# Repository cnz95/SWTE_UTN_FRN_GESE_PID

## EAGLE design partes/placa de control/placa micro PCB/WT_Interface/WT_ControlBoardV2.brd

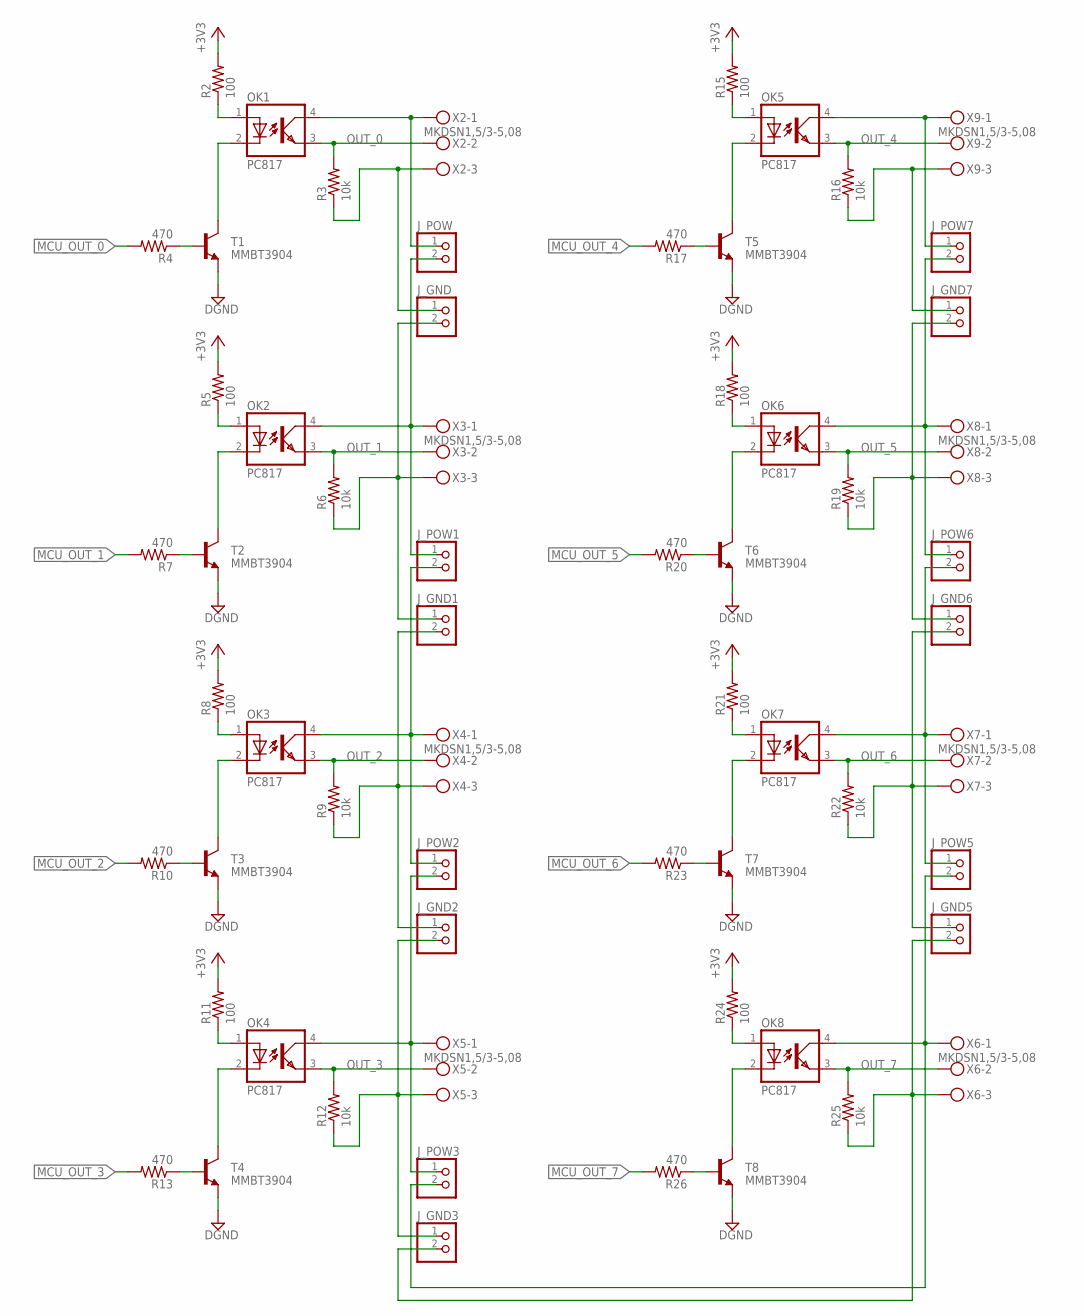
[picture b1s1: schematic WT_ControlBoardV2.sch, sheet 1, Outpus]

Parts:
J_GND, J_GND1, J_GND2, J_GND3, J_GND5, J_GND6, J_GND7: PINHD-1X2; 1X02
J_POW, J_POW1, J_POW2, J_POW3, J_POW5, J_POW6, J_POW7: PINHD-1X2; 1X02
OK1, OK2, OK3, OK4, OK5, OK6, OK7, OK8: PC817; DIL04
R2, R5, R8, R11, R15, R18, R21, R24: 100; R0402
R3, R6, R9, R12, R16, R19, R22, R25: 10k; R0402
R4, R7, R10, R13, R20, R23, R26: 470; 0204/5
R17: 470; 0204/7
T1, T2, T3, T4, T5, T6, T7, T8: MMBT3904; SOT23-BEC
X2, X3, X4, X5, X6, X7, X8, X9: MKDSN1,5/3-5,08

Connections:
+3V3: R2.2, R5.2, R8.2, R11.2, R15.2, R18.2, R21.2, R24.2; also elsewhere on the board
DGND: T1.E, T2.E, T3.E, T4.E, T5.E, T6.E, T7.E, T8.E; also elsewhere on the board
MCU_OUT_0: R4.2; also elsewhere on the board
MCU_OUT_1: R7.2; also elsewhere on the board
MCU_OUT_2: R10.2; also elsewhere on the board
MCU_OUT_3: R13.2; also elsewhere on the board
MCU_OUT_4: R17.2; also elsewhere on the board
MCU_OUT_5: R20.2; also elsewhere on the board
MCU_OUT_6: R23.2; also elsewhere on the board
MCU_OUT_7: R26.2; also elsewhere on the board
unnamed: OK1.2 (C), T1.C
unnamed: OK2.2 (C), T2.C
unnamed: R4.1, T1.B
unnamed: OK1.1 (A), R2.1
unnamed: R7.1, T2.B
unnamed: OK2.1 (A), R5.1
unnamed: OK3.2 (C), T3.C
unnamed: R10.1, T3.B
unnamed: OK3.1 (A), R8.1
unnamed: OK4.2 (C), T4.C
unnamed: R13.1, T4.B
unnamed: OK4.1 (A), R11.1
unnamed: OK5.2 (C), T5.C
unnamed: R17.1, T5.B
unnamed: OK5.1 (A), R15.1
unnamed: OK6.2 (C), T6.C
unnamed: R20.1, T6.B
unnamed: OK6.1 (A), R18.1
unnamed: OK7.2 (C), T7.C
unnamed: R23.1, T7.B
unnamed: OK7.1 (A), R21.1
unnamed: OK8.2 (C), T8.C
unnamed: R26.1, T8.B
unnamed: OK8.1 (A), R24.1
unnamed: J_GND6.1, J_GND7.2, R19.1, X8.3
unnamed: J_GND.1, R3.1, X2.3
unnamed: J_GND.2, J_GND1.1, R6.1, X3.3
unnamed: J_POW.2, J_POW1.1, OK2.4 (COL), X3.1
unnamed: J_POW1.2, J_POW2.1, OK3.4 (COL), X4.1
unnamed: J_GND1.2, J_GND2.1, R9.1, X4.3
unnamed: J_POW2.2, J_POW3.1, OK4.4 (COL), X5.1
unnamed: J_GND2.2, J_GND3.1, R12.1, X5.3
unnamed: J_GND3.2, J_GND5.2, R25.1, X6.3
unnamed: J_POW3.2, J_POW5.2, OK8.4 (COL), X6.1
unnamed: J_POW5.1, J_POW6.2, OK7.4 (COL), X7.1
unnamed: J_GND5.1, J_GND6.2, R22.1, X7.3
unnamed: J_POW6.1, J_POW7.2, OK6.4 (COL), X8.1
unnamed: J_POW7.1, OK5.4 (COL), X9.1
unnamed: J_GND7.1, R16.1, X9.3
unnamed: J_POW.1, OK1.4 (COL), X2.1
OUT_0: OK1.3 (EMIT), R3.2, X2.2
OUT_1: OK2.3 (EMIT), R6.2, X3.2
OUT_2: OK3.3 (EMIT), R9.2, X4.2
OUT_3: OK4.3 (EMIT), R12.2, X5.2
OUT_4: OK5.3 (EMIT), R16.2, X9.2
OUT_5: OK6.3 (EMIT), R19.2, X8.2
OUT_6: OK7.3 (EMIT), R22.2, X7.2
OUT_7: OK8.3 (EMIT), R25.2, X6.2

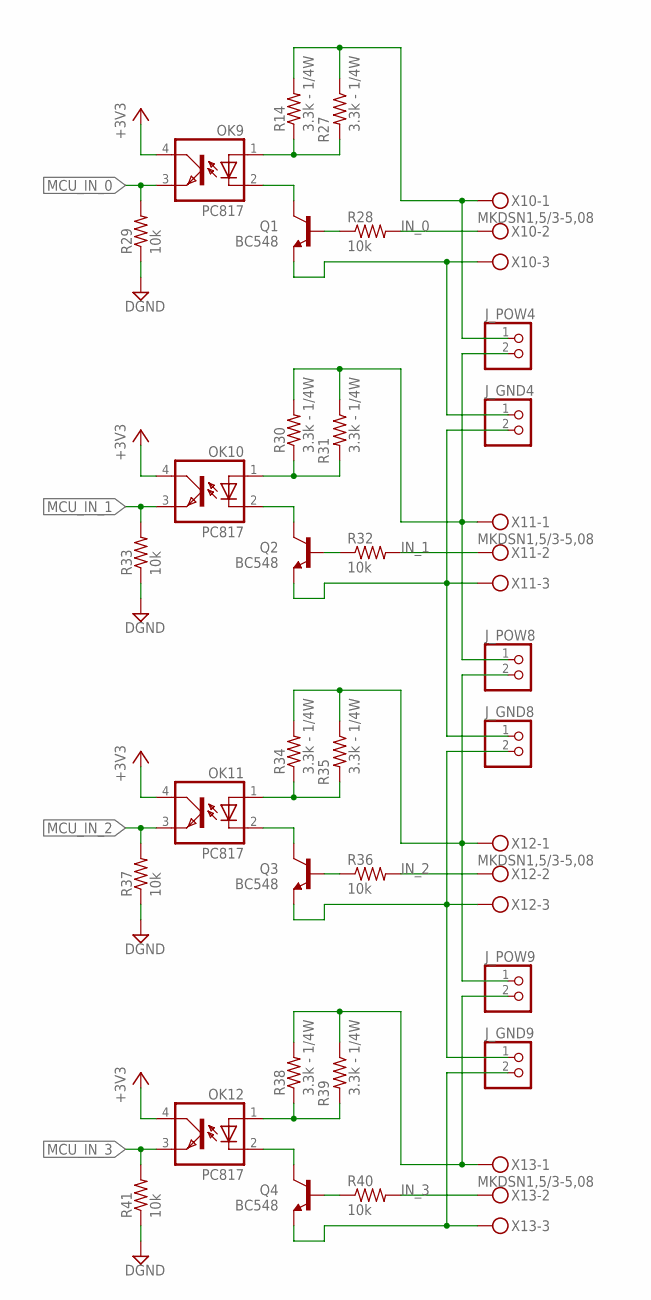
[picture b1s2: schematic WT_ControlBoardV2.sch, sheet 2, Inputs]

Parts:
J_GND4, J_GND8, J_GND9: PINHD-1X2; 1X02
J_POW4, J_POW8, J_POW9: PINHD-1X2; 1X02
OK9, OK10, OK11, OK12: PC817; DIL04
Q1, Q2, Q3, Q4: BC548; TO92-EBC
R14, R27, R30, R31, R34, R35, R38, R39: 3.3k - 1/4W; 0204V
R28, R32, R36, R40: 10k; 0204/5
R29, R33, R37, R41: 10k; R0402
X10, X11, X12, X13: MKDSN1,5/3-5,08

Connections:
+3V3: OK9.4 (COL), OK10.4 (COL), OK11.4 (COL), OK12.4 (COL); also elsewhere on the board
DGND: R29.1, R33.1, R37.1, R41.1; also elsewhere on the board
IN_0: R28.2, X10.2
IN_1: R32.2, X11.2
IN_2: R36.2, X12.2
IN_3: R40.2, X13.2
MCU_IN_0: OK9.3 (EMIT), R29.2; also elsewhere on the board
MCU_IN_1: OK10.3 (EMIT), R33.2; also elsewhere on the board
MCU_IN_2: OK11.3 (EMIT), R37.2; also elsewhere on the board
MCU_IN_3: OK12.3 (EMIT), R41.2; also elsewhere on the board
unnamed: OK9.1 (A), R14.1, R27.2
unnamed: OK9.2 (C), Q1.C
unnamed: Q1.B, R28.1
unnamed: OK10.1 (A), R30.1, R31.2
unnamed: OK10.2 (C), Q2.C
unnamed: Q2.B, R32.1
unnamed: OK11.1 (A), R34.1, R35.2
unnamed: OK11.2 (C), Q3.C
unnamed: Q3.B, R36.1
unnamed: OK12.1 (A), R38.1, R39.2
unnamed: OK12.2 (C), Q4.C
unnamed: Q4.B, R40.1
unnamed: J_GND4.2, J_GND8.1, Q2.E, X11.3
unnamed: J_GND9.2, Q4.E, X13.3
unnamed: J_POW9.2, R38.2, R39.1, X13.1
unnamed: J_POW4.2, J_POW8.1, R30.2, R31.1, X11.1
unnamed: J_GND8.2, J_GND9.1, Q3.E, X12.3
unnamed: J_POW8.2, J_POW9.1, R34.2, R35.1, X12.1
unnamed: J_GND4.1, Q1.E, X10.3
unnamed: J_POW4.1, R14.2, R27.1, X10.1

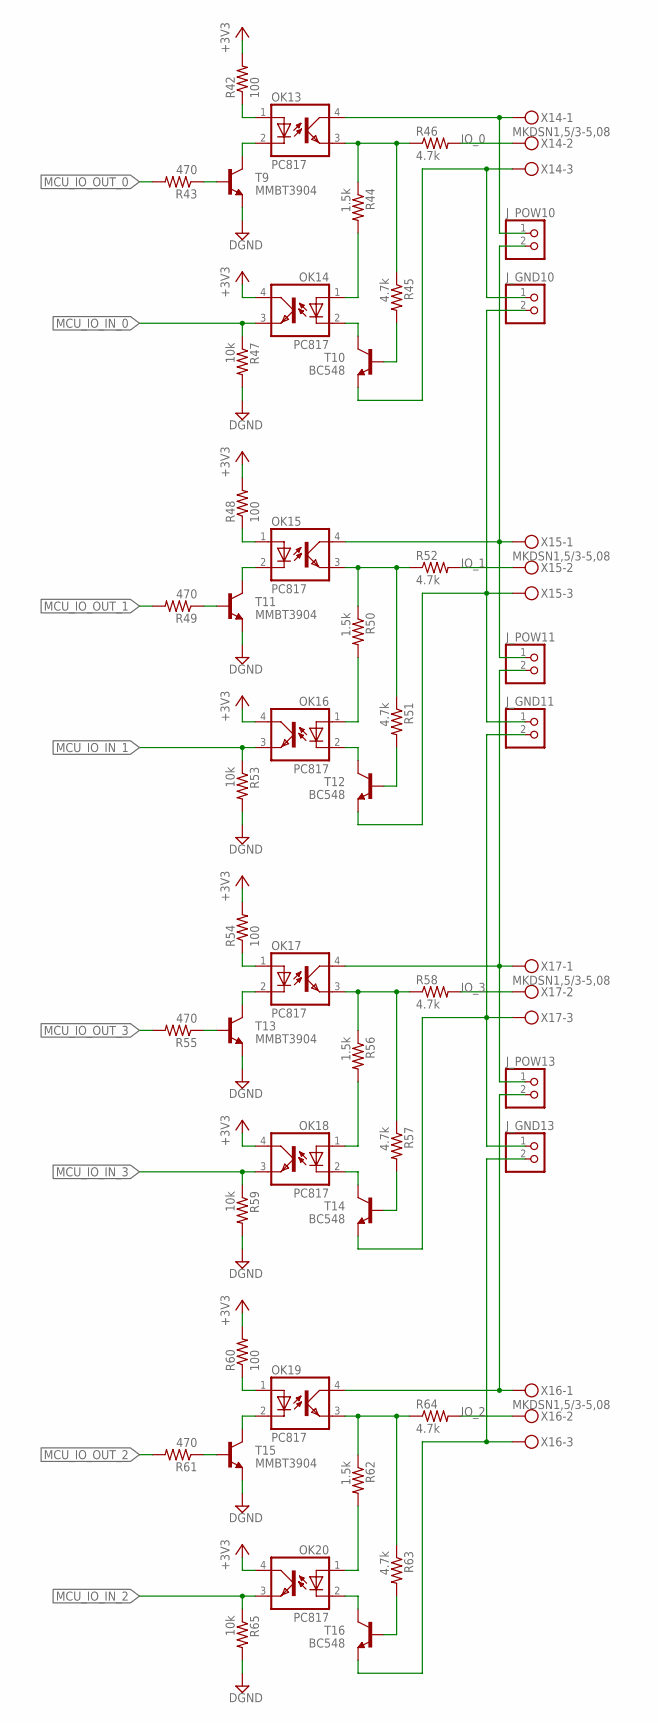
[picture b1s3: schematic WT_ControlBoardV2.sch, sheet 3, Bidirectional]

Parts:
J_GND10, J_GND11, J_GND13: PINHD-1X2; 1X02
J_POW10, J_POW11, J_POW13: PINHD-1X2; 1X02
OK13, OK14, OK15, OK16, OK17, OK18, OK19, OK20: PC817; DIL04
R42, R48, R54, R60: 100; 0204/7
R43, R49, R55, R61: 470; R0402
R44, R50, R56, R62: 1.5k; 0204/5
R45, R46, R51, R52, R57, R58, R63, R64: 4.7k; 0204V
R47, R53, R59, R65: 10k; 0204/5
T9, T11, T13, T15: MMBT3904; SOT23-BEC
T10, T12, T14, T16: BC548; TO92-CBE
X14, X15, X16, X17: MKDSN1,5/3-5,08

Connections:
+3V3: OK14.4 (COL), OK16.4 (COL), OK18.4 (COL), OK20.4 (COL), R42.2, R48.2, R54.2, R60.2; also elsewhere on the board
DGND: R47.2, R53.2, R59.2, R65.2, T9.E, T11.E, T13.E, T15.E; also elsewhere on the board
IO_0: R46.2, X14.2
IO_1: R52.2, X15.2
IO_2: R64.2, X16.2
IO_3: R58.2, X17.2
MCU_IO_IN_0: OK14.3 (EMIT), R47.1; also elsewhere on the board
MCU_IO_IN_1: OK16.3 (EMIT), R53.1; also elsewhere on the board
MCU_IO_IN_2: OK20.3 (EMIT), R65.1; also elsewhere on the board
MCU_IO_IN_3: OK18.3 (EMIT), R59.1; also elsewhere on the board
MCU_IO_OUT_0: R43.2; also elsewhere on the board
MCU_IO_OUT_1: R49.2; also elsewhere on the board
MCU_IO_OUT_2: R61.2; also elsewhere on the board
MCU_IO_OUT_3: R55.2; also elsewhere on the board
unnamed: OK14.2 (C), T10.C
unnamed: OK13.2 (C), T9.C
unnamed: R43.1, T9.B
unnamed: OK13.1 (A), R42.1
unnamed: OK13.3 (EMIT), R44.1, R45.1, R46.1
unnamed: OK14.1 (A), R44.2
unnamed: R45.2, T10.B
unnamed: OK16.2 (C), T12.C
unnamed: OK15.2 (C), T11.C
unnamed: R49.1, T11.B
unnamed: OK15.1 (A), R48.1
unnamed: OK15.3 (EMIT), R50.1, R51.1, R52.1
unnamed: OK16.1 (A), R50.2
unnamed: R51.2, T12.B
unnamed: OK18.2 (C), T14.C
unnamed: OK17.2 (C), T13.C
unnamed: R55.1, T13.B
unnamed: OK17.1 (A), R54.1
unnamed: OK17.3 (EMIT), R56.1, R57.1, R58.1
unnamed: OK18.1 (A), R56.2
unnamed: R57.2, T14.B
unnamed: OK20.2 (C), T16.C
unnamed: OK19.2 (C), T15.C
unnamed: R61.1, T15.B
unnamed: OK19.1 (A), R60.1
unnamed: OK19.3 (EMIT), R62.1, R63.1, R64.1
unnamed: OK20.1 (A), R62.2
unnamed: R63.2, T16.B
unnamed: J_POW11.2, J_POW13.1, OK17.4 (COL), X17.1
unnamed: J_GND13.2, T16.E, X16.3
unnamed: J_POW10.1, OK13.4 (COL), X14.1
unnamed: J_GND10.1, T10.E, X14.3
unnamed: J_POW10.2, J_POW11.1, OK15.4 (COL), X15.1
unnamed: J_GND10.2, J_GND11.1, T12.E, X15.3
unnamed: J_GND11.2, J_GND13.1, T14.E, X17.3
unnamed: J_POW13.2, OK19.4 (COL), X16.1

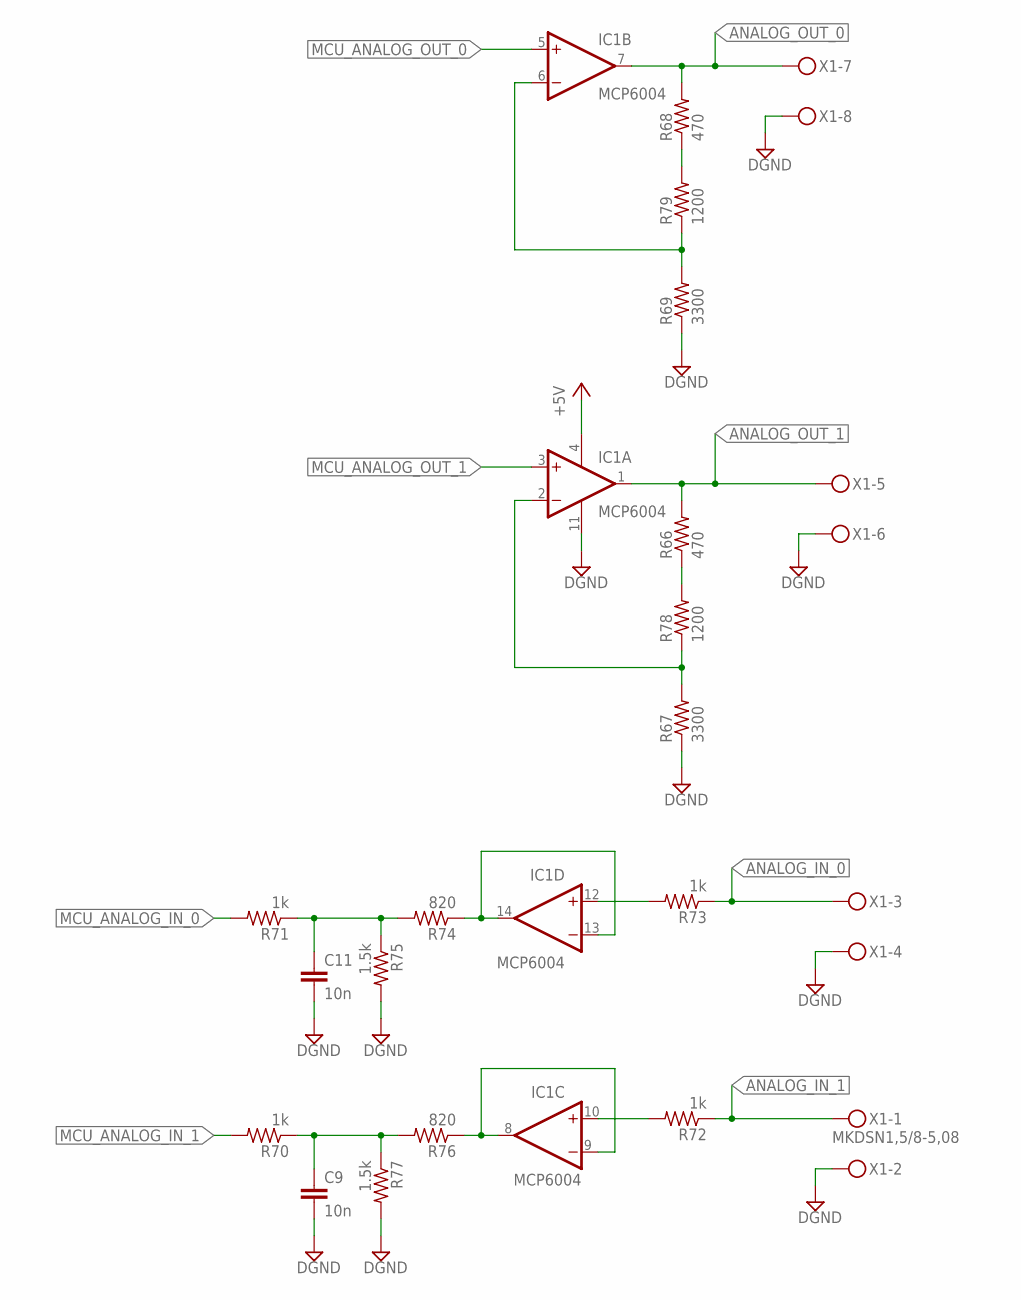
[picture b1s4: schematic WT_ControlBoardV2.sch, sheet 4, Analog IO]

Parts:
C9, C11: 10n; C0402
IC1: MCP6004; SO14
R66, R68: 470; R0402
R67, R69: 3300; R0402
R70, R71: 1k; R0402
R72: 1k; 0204V
R73: 1k; 0204/7
R74, R76: 820; R0402
R75, R77: 1.5k; R0402
R78, R79: 1200; R0402
X1: MKDSN1,5/8-5,08

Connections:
+5V: IC1.4 (V+); also elsewhere on the board
ANALOG_IN_0: R73.1, X1.3
ANALOG_IN_1: R72.1, X1.1
ANALOG_OUT_0: IC1.7 (OUT), R68.2, X1.7
ANALOG_OUT_1: IC1.1 (OUT), R66.2, X1.5
DGND: C9.2, C11.2, IC1.11 (V-), R67.1, R69.1, R75.2, R77.2, X1.2, X1.4, X1.6, X1.8; also elsewhere on the board
MCU_ANALOG_IN_0: R71.2; also elsewhere on the board
MCU_ANALOG_IN_1: R70.2; also elsewhere on the board
MCU_ANALOG_OUT_0: IC1.5 (+IN); also elsewhere on the board
MCU_ANALOG_OUT_1: IC1.3 (+IN); also elsewhere on the board
unnamed: IC1.6 (-IN), R69.2, R79.1
unnamed: IC1.2 (-IN), R67.2, R78.1
unnamed: IC1.10 (+IN), R72.2
unnamed: IC1.12 (+IN), R73.2
unnamed: IC1.8 (OUT), IC1.9 (-IN), R76.1
unnamed: IC1.13 (-IN), IC1.14 (OUT), R74.1
unnamed: C9.1, R70.1, R76.2, R77.1
unnamed: C11.1, R71.1, R74.2, R75.1
unnamed: R66.1, R78.2
unnamed: R68.1, R79.2

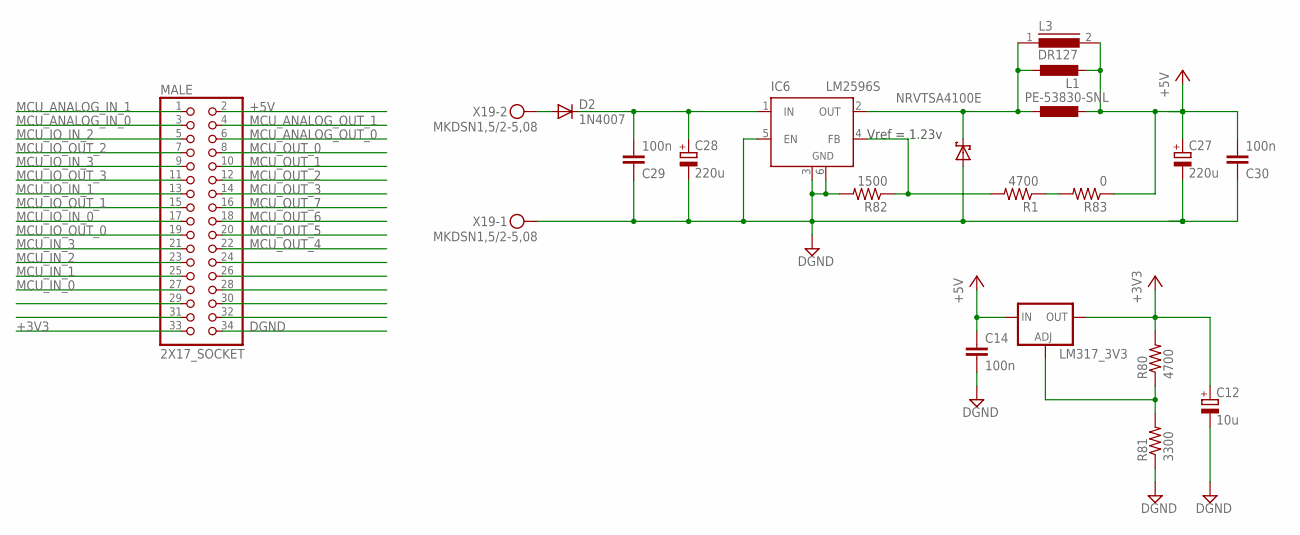
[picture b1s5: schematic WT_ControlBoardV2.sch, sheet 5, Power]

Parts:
C12: 10u; E1,8-4
C14, C29, C30: 100n; C1206
C27, C28: 220u; E5-10,5
D2: 1N4007; C1702-05
D8: NRVTSA4100E; SMA-2
IC6: LM2596S; TO263-5
L1: L-EUPIS2816; PIS2816
L2: PE-53830-SNL; LCI-44
L3: DR127
LM317_3V3: LM317TS; 317TS
MALE: 2X17_SOCKET
R1: 4700; R0402
R80: 4700; 0204V
R81: 3300; 0204V
R82: 1500; R0402
R83: 0; R0402
X19: MKDSN1,5/2-5,08

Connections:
+3V3: C12.+, LM317_3V3.2 (OUT), MALE.33, R80.2; also elsewhere on the board
+5V: C14.1, C27.+, C30.2, L1.2, L2.1, L3.2, LM317_3V3.3 (IN), MALE.2, R83.1; also elsewhere on the board
DGND: C12.-, C14.2, C27.-, C28.-, C29.1, C30.1, D8.A, IC6.3 (GND), IC6.5 (EN), IC6.6 (GND), MALE.34, R81.1, R82.2, X19.1; also elsewhere on the board
MCU_ANALOG_IN_0: MALE.3; also elsewhere on the board
MCU_ANALOG_IN_1: MALE.1; also elsewhere on the board
MCU_ANALOG_OUT_0: MALE.6; also elsewhere on the board
MCU_ANALOG_OUT_1: MALE.4; also elsewhere on the board
MCU_IN_0: MALE.27; also elsewhere on the board
MCU_IN_1: MALE.25; also elsewhere on the board
MCU_IN_2: MALE.23; also elsewhere on the board
MCU_IN_3: MALE.21; also elsewhere on the board
MCU_IO_IN_0: MALE.17; also elsewhere on the board
MCU_IO_IN_1: MALE.13; also elsewhere on the board
MCU_IO_IN_2: MALE.5; also elsewhere on the board
MCU_IO_IN_3: MALE.9; also elsewhere on the board
MCU_IO_OUT_0: MALE.19; also elsewhere on the board
MCU_IO_OUT_1: MALE.15; also elsewhere on the board
MCU_IO_OUT_2: MALE.7; also elsewhere on the board
MCU_IO_OUT_3: MALE.11; also elsewhere on the board
MCU_OUT_0: MALE.8; also elsewhere on the board
MCU_OUT_1: MALE.10; also elsewhere on the board
MCU_OUT_2: MALE.12; also elsewhere on the board
MCU_OUT_3: MALE.14; also elsewhere on the board
MCU_OUT_4: MALE.22; also elsewhere on the board
MCU_OUT_5: MALE.20; also elsewhere on the board
MCU_OUT_6: MALE.18; also elsewhere on the board
MCU_OUT_7: MALE.16; also elsewhere on the board
unnamed: D2.A, X19.2
unnamed: D8.C, IC6.2 (OUT), L1.1, L2.2, L3.1
unnamed: C28.+, C29.2, D2.C, IC6.1 (IN)
unnamed: LM317_3V3.1 (ADJ), R80.1, R81.2
unnamed: IC6.4 (FB), R1.2, R82.1
unnamed: R1.1, R83.2

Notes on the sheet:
Vref = 1.23v

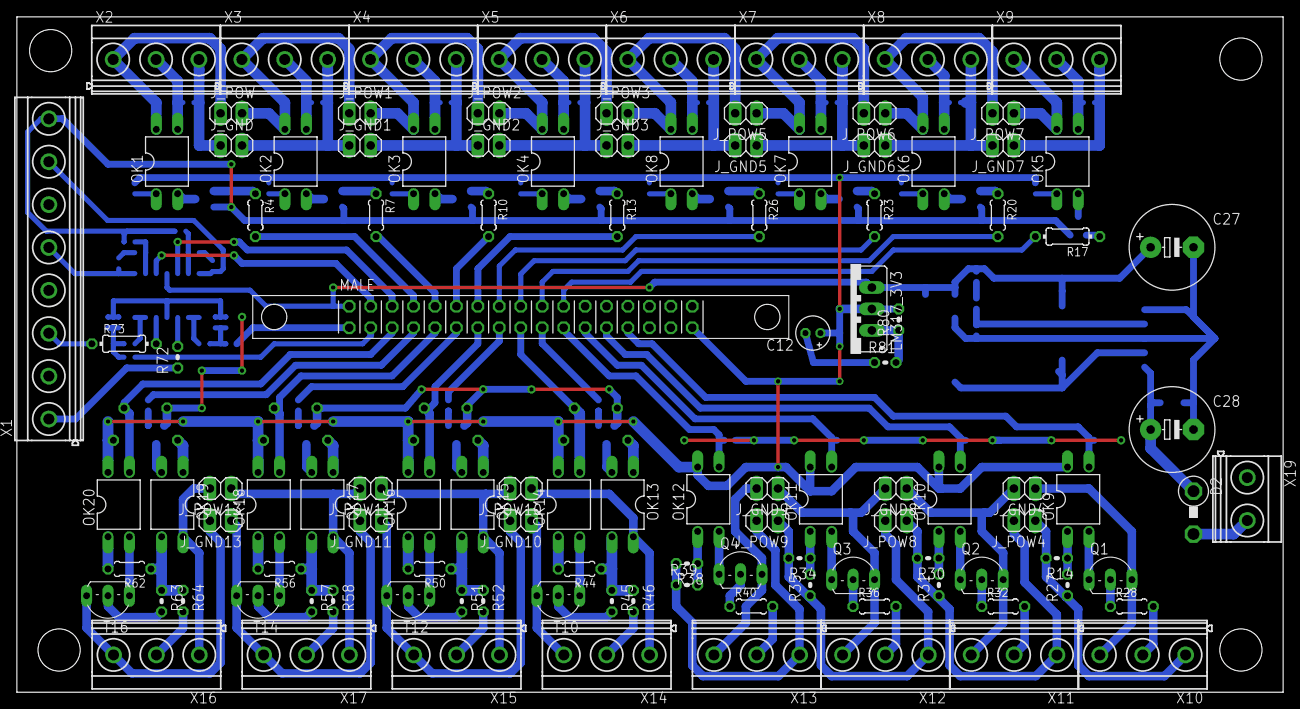
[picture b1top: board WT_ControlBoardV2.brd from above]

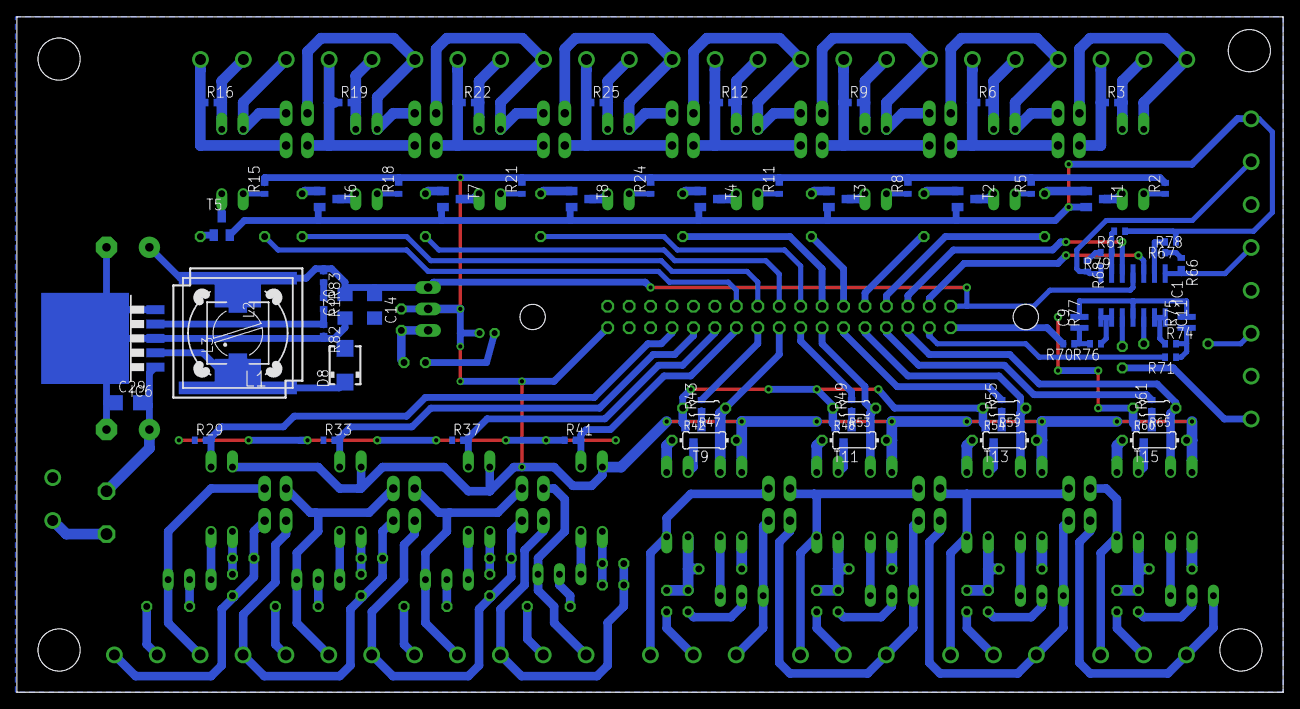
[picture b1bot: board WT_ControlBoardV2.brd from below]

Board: 2 copper layers, 150.0 x 80.0 mm, 184 parts (70 on the bottom side), 159 nets.

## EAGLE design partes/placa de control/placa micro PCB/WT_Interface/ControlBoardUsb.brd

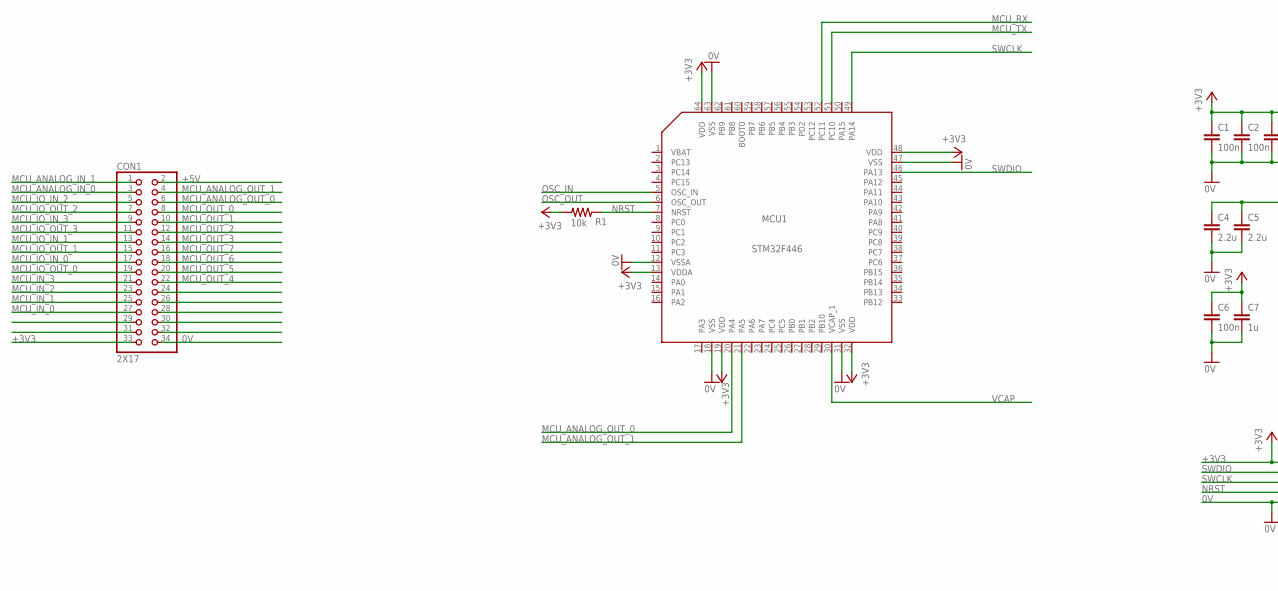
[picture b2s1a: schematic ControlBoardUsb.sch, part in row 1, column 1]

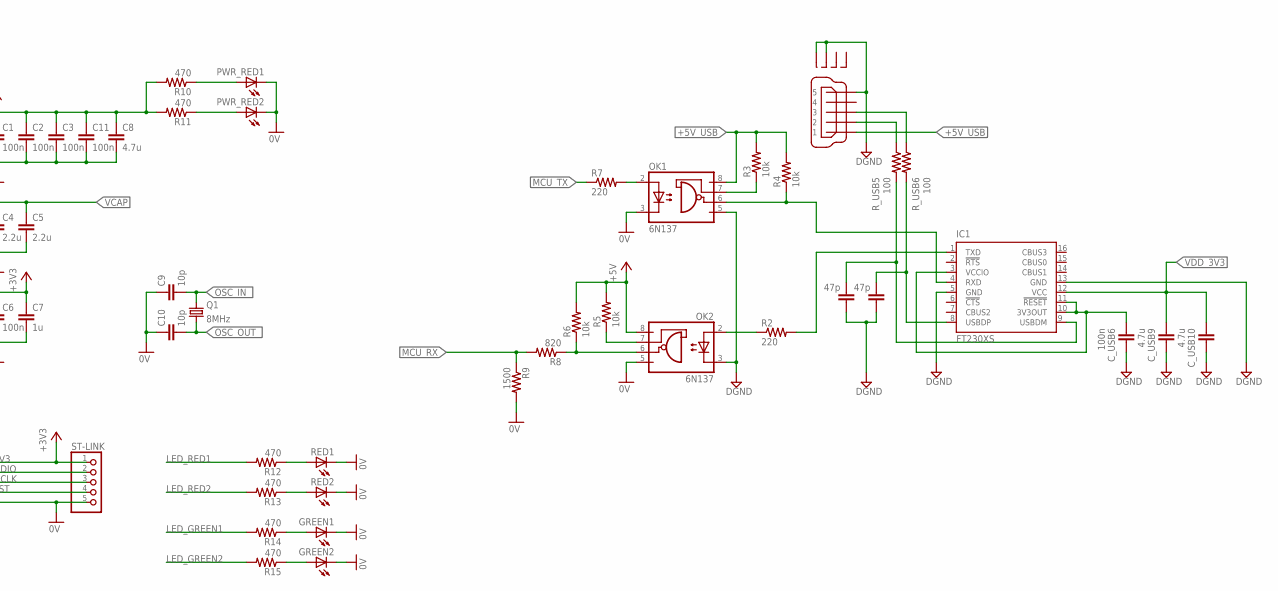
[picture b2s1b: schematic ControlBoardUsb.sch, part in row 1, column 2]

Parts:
C1, C2, C3, C6, C11: 100n; C0402
C4, C5: 2.2u; C0402
C7: 1u; C0402
C8: 4.7u; C0402
C9, C10: 10p; C0402
CON1: 2X17
CON3: MICRO_USB_TYPE_A; MINI_USB_TYPE_A_THOLE
C_USB6: 100n; C0402
C_USB7, C_USB8: 47p; C0402
C_USB9, C_USB10: 4.7u; C0402
GREEN1, GREEN2: LEDCHIP-LED0805; CHIP-LED0805
IC1: FT230XS; SSOP16
MCU1: STM32F446; LQFP-64
OK1, OK2: 6N137; DIL08
PWR_RED1, PWR_RED2: LEDCHIP-LED0805; CHIP-LED0805
Q1: 8MHz; HC33U-V
R1, R3, R4, R5, R6: 10k; R0402
R2, R7: 220; R0402
R8: 820; R0402
R9: 1500; R0402
R10, R11, R12, R13, R14, R15: 470; R0402
RED1, RED2: LEDCHIP-LED0805; CHIP-LED0805
R_USB5, R_USB6: 100; R0402
ST-LINK: PINHD-1X5/90; 1X05/90

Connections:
0V: C1.2, C2.2, C3.2, C4.2, C5.2, C6.2, C7.2, C8.2, C9.1, C10.1, C11.2, CON1.34, GREEN1.C, GREEN2.C, MCU1.12 (VSSA), MCU1.18 (VSS), MCU1.31 (VSS), MCU1.47 (VSS), MCU1.63 (VSS), OK1.3 (C), OK2.5 (GND), PWR_RED1.C, PWR_RED2.C, R9.2, RED1.C, RED2.C, ST-LINK.5
+3V3: C1.1, C2.1, C3.1, C6.1, C7.1, C8.1, C11.1, CON1.33, MCU1.13 (VDDA), MCU1.19 (VDD), MCU1.32 (VDD), MCU1.48 (VDD), MCU1.64 (VDD), R1.2, R10.2, R11.2, ST-LINK.1
+5V: CON1.2, OK2.8 (VCC), R5.2, R6.2
+5V_USB: CON3.1, OK1.8 (VCC), R3.2, R4.2
DGND: CON3.5, CON3.M3 (S3), CON3.M4 (S4), C_USB6.1, C_USB7.1, C_USB8.1, C_USB9.1, C_USB10.1, IC1.5 (GND), IC1.13 (GND), OK1.5 (GND), OK2.3 (C)
LED_GREEN1: R14.2
LED_GREEN2: R15.2
LED_RED1: R12.2
LED_RED2: R13.2
MCU_ANALOG_IN_0: CON1.3
MCU_ANALOG_IN_1: CON1.1
MCU_ANALOG_OUT_0: CON1.6, MCU1.20 (PA4)
MCU_ANALOG_OUT_1: CON1.4, MCU1.21 (PA5)
MCU_IN_0: CON1.27
MCU_IN_1: CON1.25
MCU_IN_2: CON1.23
MCU_IN_3: CON1.21
MCU_IO_IN_0: CON1.17
MCU_IO_IN_1: CON1.13
MCU_IO_IN_2: CON1.5
MCU_IO_IN_3: CON1.9
MCU_IO_OUT_0: CON1.19
MCU_IO_OUT_1: CON1.15
MCU_IO_OUT_2: CON1.7
MCU_IO_OUT_3: CON1.11
MCU_OUT_0: CON1.8
MCU_OUT_1: CON1.10
MCU_OUT_2: CON1.12
MCU_OUT_3: CON1.14
MCU_OUT_4: CON1.22
MCU_OUT_5: CON1.20
MCU_OUT_6: CON1.18
MCU_OUT_7: CON1.16
MCU_RX: MCU1.52 (PC11), R8.2, R9.1
MCU_TX: MCU1.51 (PC10), R7.1
unnamed: OK2.2 (A), R2.1
unnamed: OK2.6 (VO), R6.1, R8.1
unnamed: OK2.7 (VE), R5.1
unnamed: OK1.7 (VE), R3.1
unnamed: PWR_RED1.A, R10.1
unnamed: OK1.2 (A), R7.2
unnamed: PWR_RED2.A, R11.1
unnamed: R12.1, RED1.A
unnamed: R13.1, RED2.A
unnamed: C_USB6.2, IC1.3 (VCCIO), IC1.10 (3V3OUT), IC1.11 (!RESET)
unnamed: GREEN1.A, R14.1
unnamed: GREEN2.A, R15.1
unnamed: C_USB8.2, IC1.8 (USBDP), R_USB6.2
unnamed: C_USB7.2, IC1.9 (USBDM), R_USB5.2
unnamed: CON3.2, R_USB5.1
unnamed: CON3.3, R_USB6.1
NRST: MCU1.7 (NRST), R1.1, ST-LINK.4
OSC_IN: MCU1.5 (OSC_IN)
OSC_IN_: C9.2, Q1.2
OSC_OUT: MCU1.6 (OSC_OUT)
OSC_OUT_: C10.2, Q1.1
SWCLK: MCU1.49 (PA14), ST-LINK.3
SWDIO: MCU1.46 (PA13), ST-LINK.2
UART4_RX: IC1.1 (TXD), R2.2
UART4_TX: IC1.4 (RXD), OK1.6 (VO), R4.1
VCAP: C4.1, C5.1, MCU1.30 (VCAP_1)
VDD_3V3: C_USB9.2, C_USB10.2, IC1.12 (VCC)

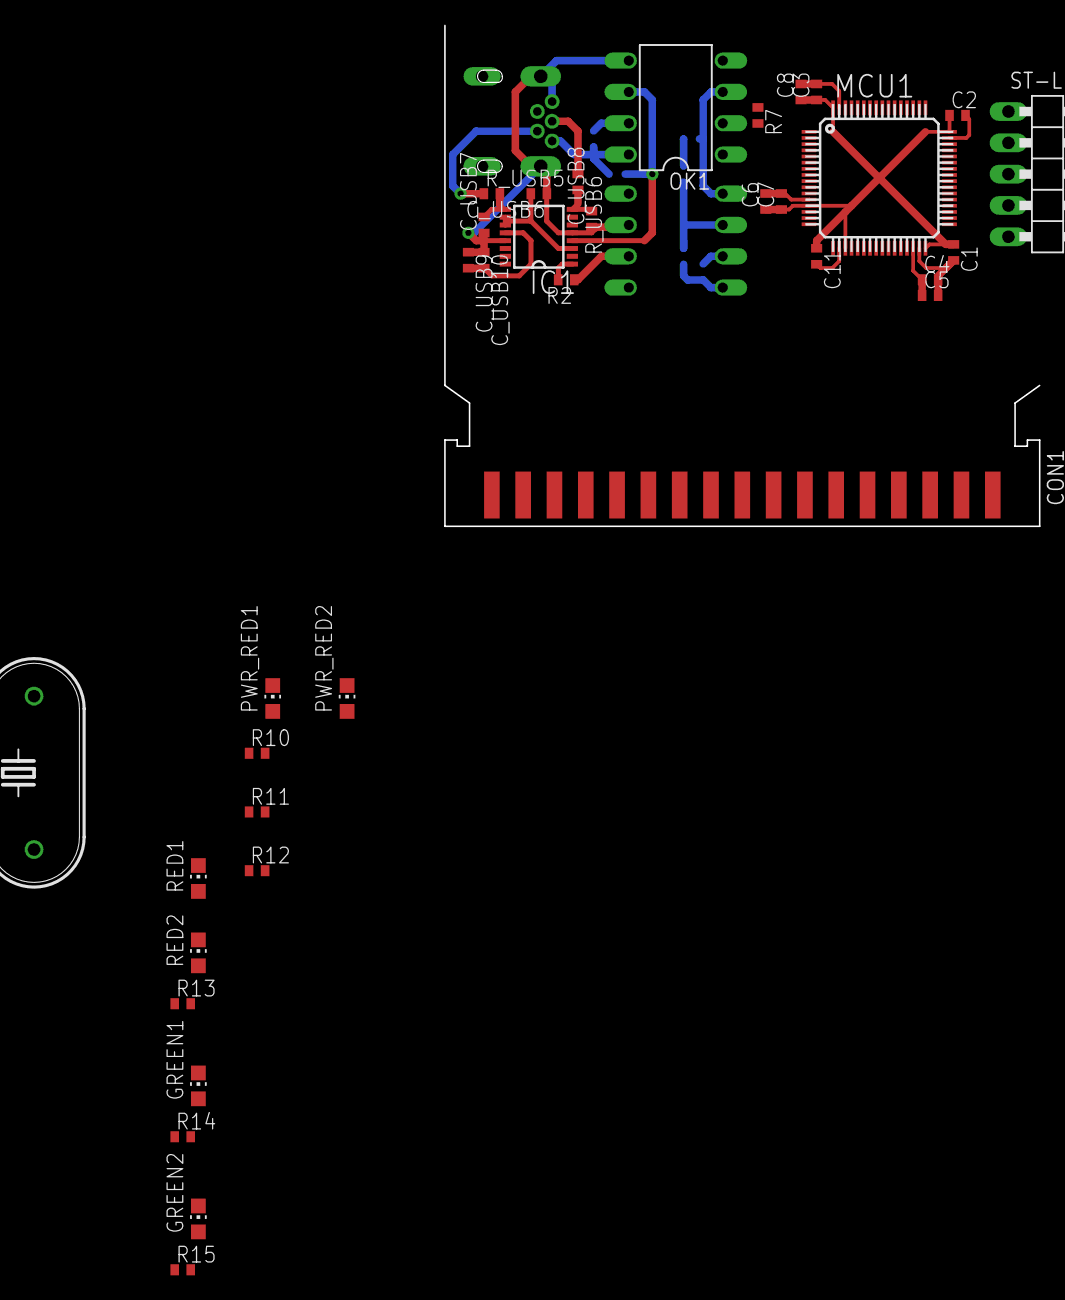
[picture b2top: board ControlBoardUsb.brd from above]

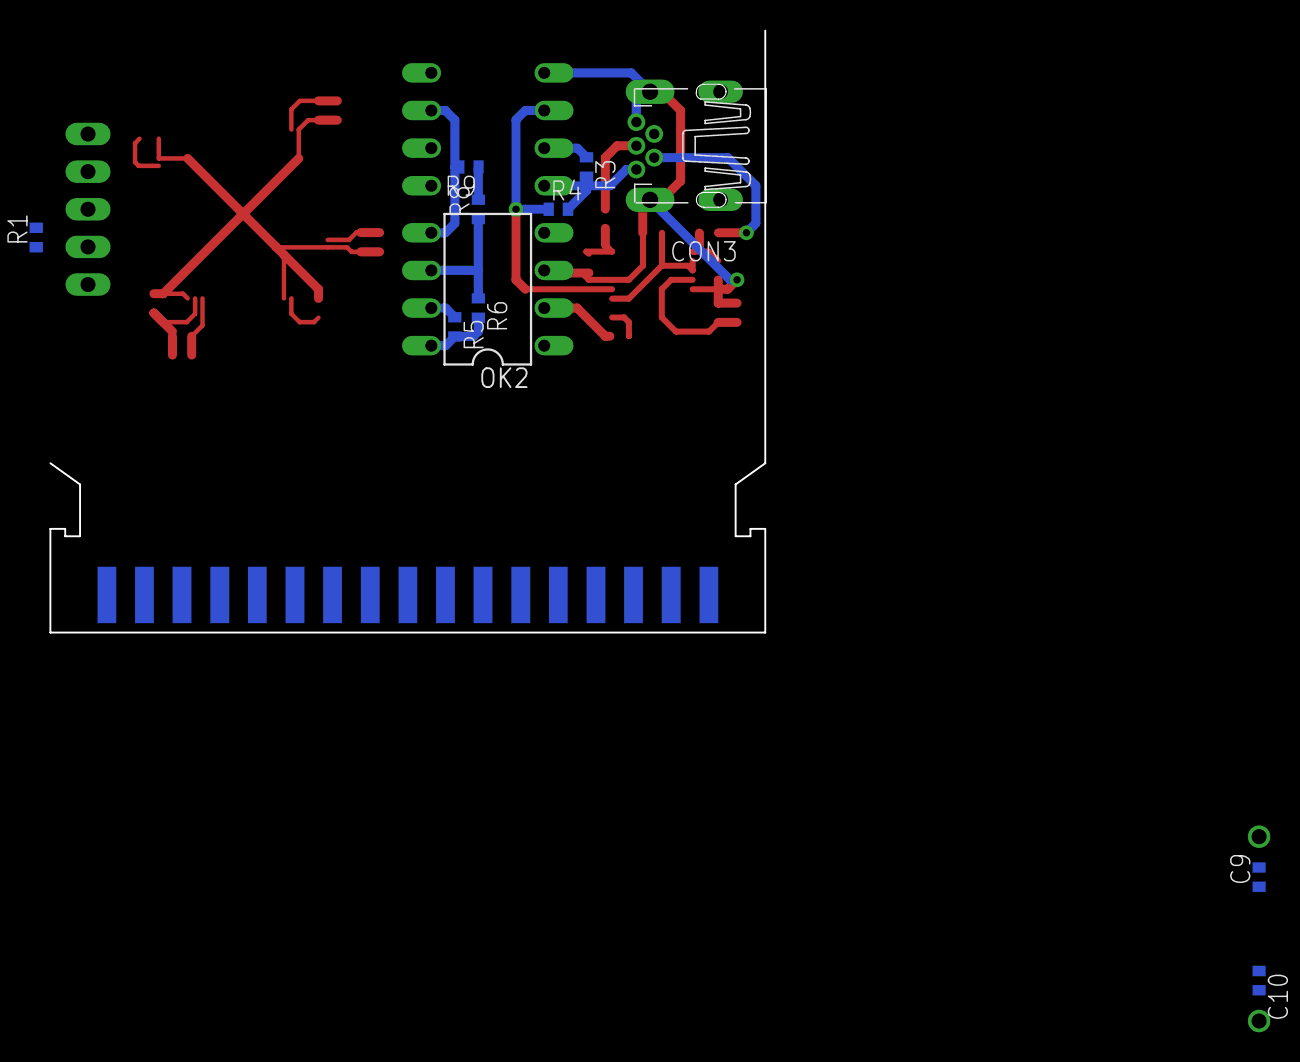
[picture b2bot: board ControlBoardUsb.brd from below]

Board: 2 copper layers, 47 parts (11 on the bottom side), 34 nets.
